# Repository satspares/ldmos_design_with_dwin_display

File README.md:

Work in progress! since 2021

28th April 2026.
New Software and PCB
Improve Graphics.
Add save drive settings per. band.

LDMOS control software and PCB design for dxworld - QRPblog A600 - or similar amps using DWIN display.

PCB design used Kicad.

Software vscode and platformio.

From the DWIN store on aliexpress

DMG80480C050_04W 5inch we need touch version DMG80480C050_04WTC  800x480

DMG80480T050_A5W more cost has case speaker and rs232

DMG80480C043_02W 4.3 inch 800x480 I have this one a bit small for big fingers.

The WTC at the end of the part number is capacitive touch or WTR is resistive touch both are ok but the WTC versions are more sensitive.
Obviously make sure you get a touch version!
Caution some of the displays have a solder link to move from rs232 to ttl.

Some of the later work here is from the excellent ideas of S21RC

G4UFI

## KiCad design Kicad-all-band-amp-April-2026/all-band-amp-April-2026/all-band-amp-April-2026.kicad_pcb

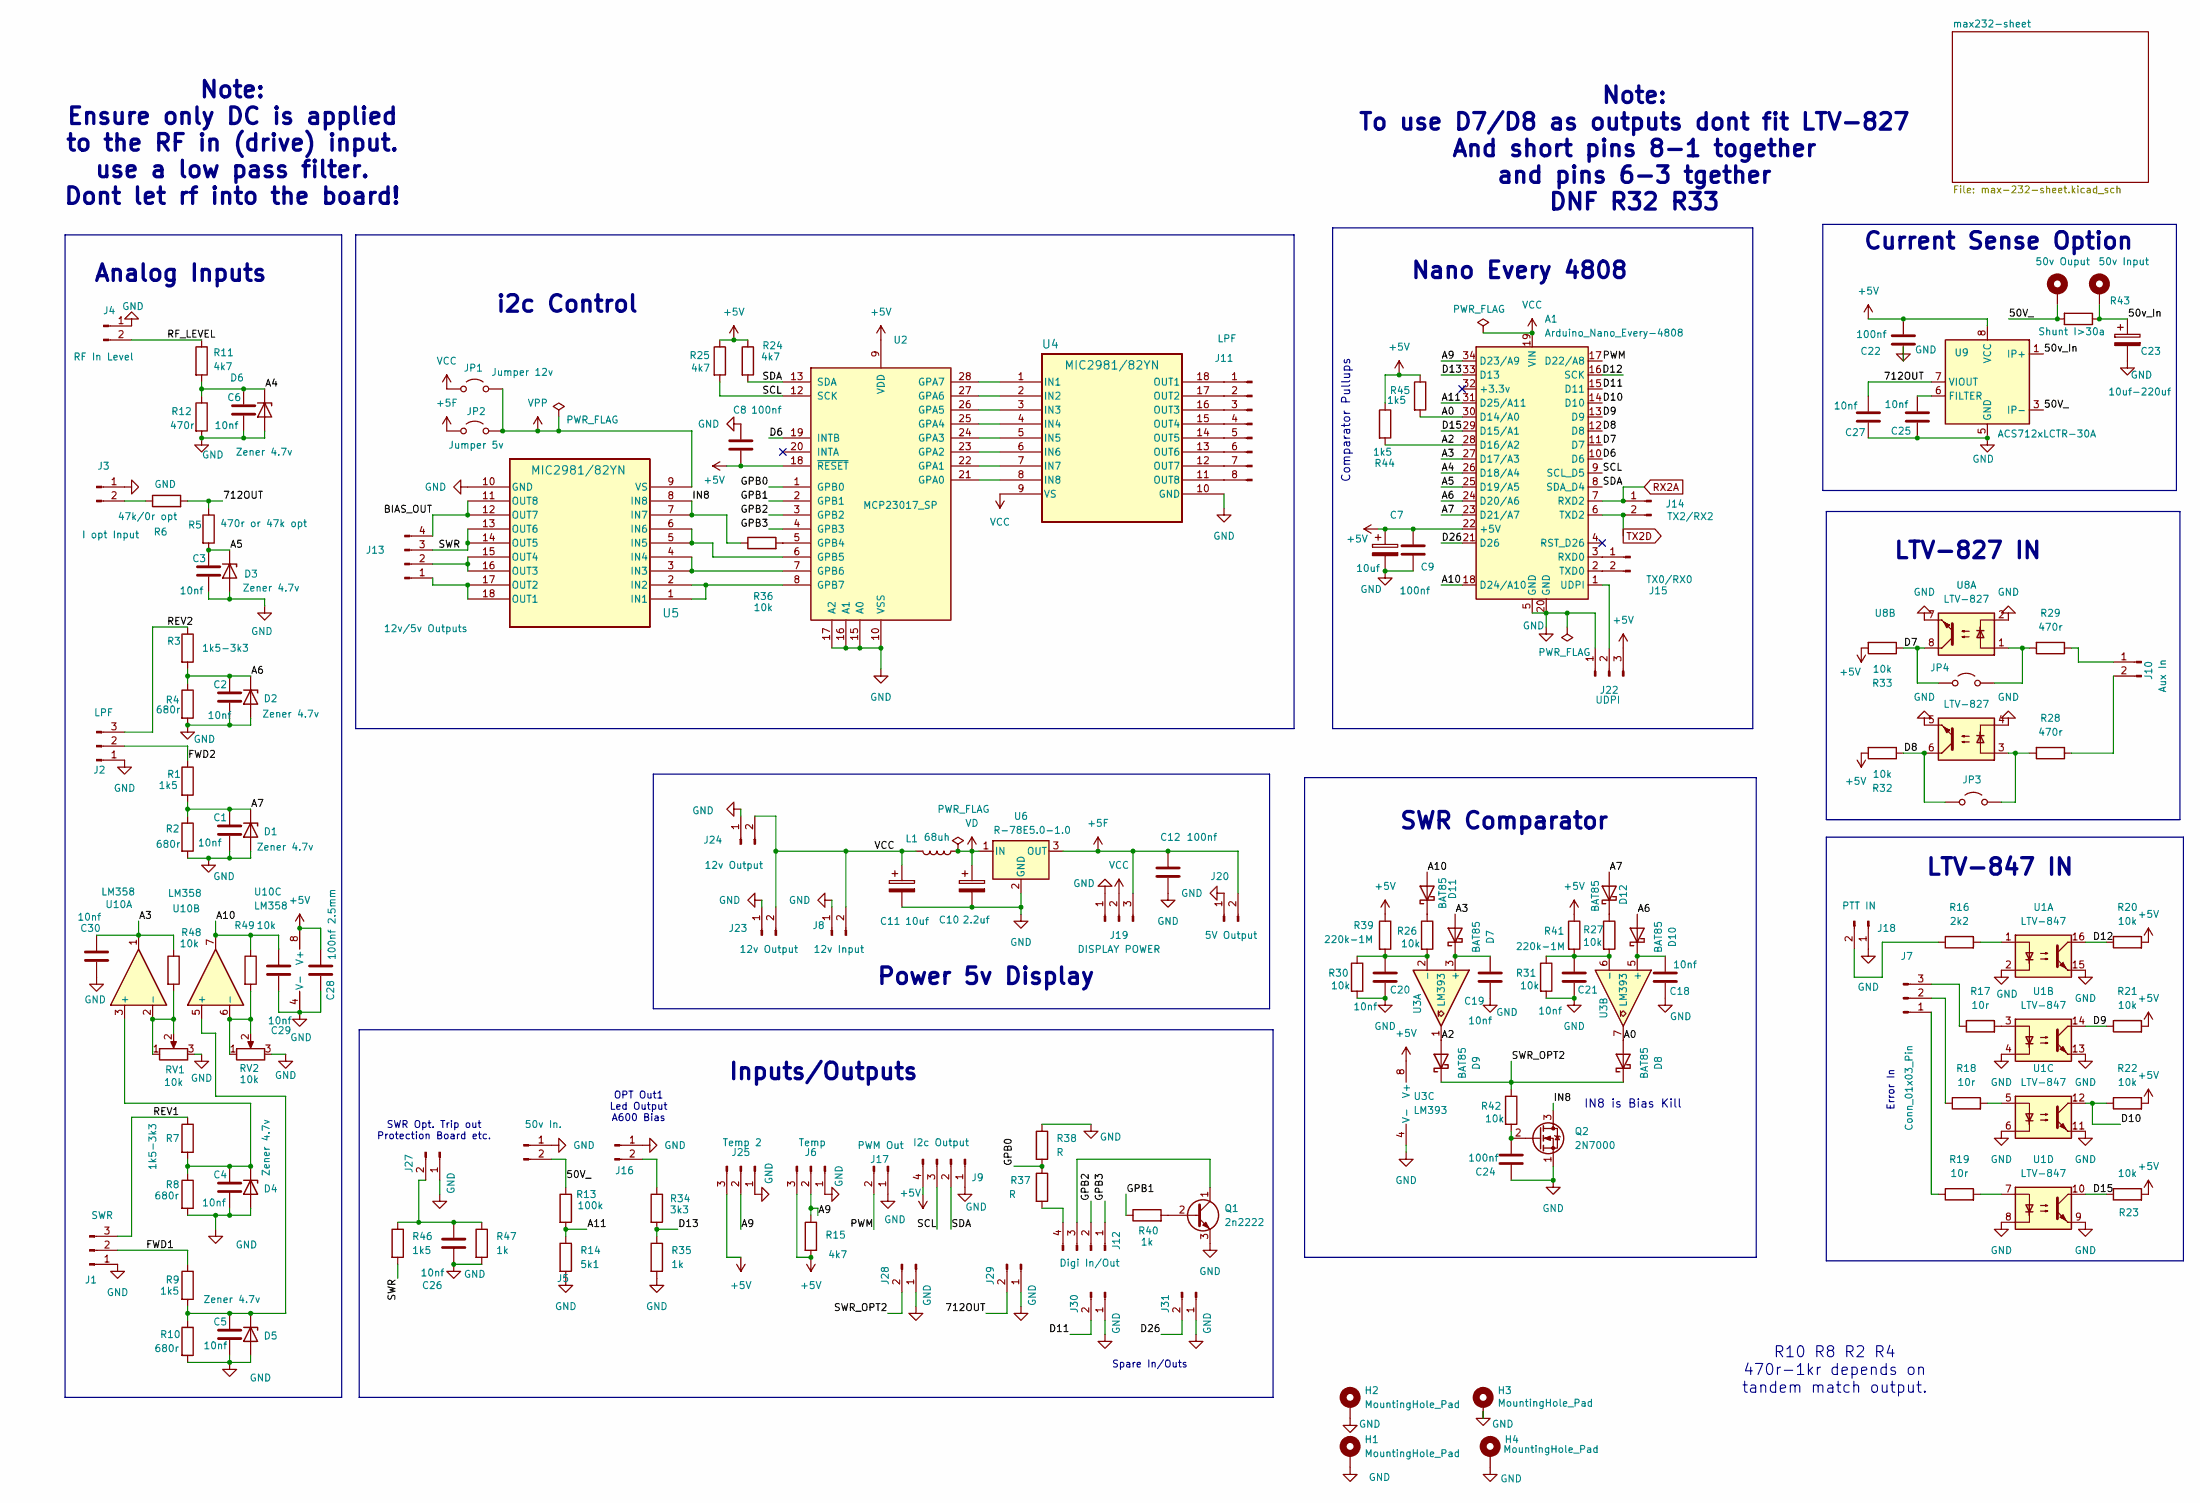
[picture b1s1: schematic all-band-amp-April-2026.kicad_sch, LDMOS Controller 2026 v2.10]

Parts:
A1: Arduino_Nano_Every-4808; DIP-34_W15.24mm
C1, C2, C3, C4, C5, C6, C18, C19, C20, C21, C25, C26, C27, C29, C30: 10nf; C_Disc_D3.4mm_W2.1mm_P2.50mm
C7, C11: 10uf; CP_Radial_D5.0mm_P2.00mm
C8, C9, C12, C22, C24: 100nf; C_Disc_D6.0mm_W2.5mm_P5.00mm
C10: 2.2uf; CP_Radial_D5.0mm_P2.00mm
C23: 10uf-220uf; CP_Radial_D10.0mm_P5.00mm
C28: 100nf 2.5mm; C_Disc_D3.4mm_W2.1mm_P2.50mm
D1, D2, D3, D4, D5, D6: Zener 4.7v; D_DO-35_SOD27_P7.62mm_Horizontal
D7, D8, D9, D10, D11, D12: BAT85; D_DO-35_SOD27_P7.62mm_Horizontal
H1, H2, H3, H4: MountingHole_Pad; MountingHole_3.5mm_Pad_Via
H5: 50v Ouput; PowerPad9mm
H6: 50v Input; PowerPad9mm
J1: SWR; JST_EH_B3B-EH-A_1x03_P2.50mm_Vertical
J2: LPF; JST_EH_B3B-EH-A_1x03_P2.50mm_Vertical
J3: I opt Input; JST_EH_B2B-EH-A_1x02_P2.50mm_Vertical
J4: RF In Level; JST_EH_B2B-EH-A_1x02_P2.50mm_Vertical
J5, J16: 50v In.; JST_EH_B2B-EH-A_1x02_P2.50mm_Vertical
J6: Temp; JST_EH_B3B-EH-A_1x03_P2.50mm_Vertical
J7: Conn_01x03_Pin; JST_EH_B3B-EH-A_1x03_P2.50mm_Vertical
J8: 12v Input; JST_EH_B2B-EH-A_1x02_P2.50mm_Vertical
J9: I2c Output; JST_EH_B4B-EH-A_1x04_P2.50mm_Vertical
J10: Aux In; JST_EH_B2B-EH-A_1x02_P2.50mm_Vertical
J11: LPF; JST_EH_B8B-EH-A_1x08_P2.50mm_Vertical
J12: Digi In/Out; JST_EH_B4B-EH-A_1x04_P2.50mm_Vertical
J13: 12v/5v Outputs; JST_EH_B4B-EH-A_1x04_P2.50mm_Vertical
J14: TX2/RX2; JST_EH_B2B-EH-A_1x02_P2.50mm_Vertical
J15: TX0/RX0; JST_EH_B2B-EH-A_1x02_P2.50mm_Vertical
J17: PWM Out; JST_EH_B2B-EH-A_1x02_P2.50mm_Vertical
J18: PTT IN; JST_EH_B2B-EH-A_1x02_P2.50mm_Vertical
J19: DISPLAY POWER; JST_EH_B3B-EH-A_1x03_P2.50mm_Vertical
J20: 5V Output; JST_EH_B2B-EH-A_1x02_P2.50mm_Vertical
J22: UDPI; JST_EH_B3B-EH-A_1x03_P2.50mm_Vertical
J23, J24: 12v Output; JST_EH_B2B-EH-A_1x02_P2.50mm_Vertical
J25: Temp 2; JST_EH_B3B-EH-A_1x03_P2.50mm_Vertical
J27, J28, J29, J30, J31: SWR trip out; JST_EH_B2B-EH-A_1x02_P2.50mm_Vertical
JP1: Jumper 12v; SolderWire-0.5sqmm_1x02_P4.8mm_D0.9mm_OD2.3mm
JP2: Jumper 5v; SolderWire-0.5sqmm_1x02_P4.8mm_D0.9mm_OD2.3mm
JP3, JP4: Jumper_2_Open; SolderJumper-2_P1.3mm_Open_TrianglePad1.0x1.5mm-mod
L1: 68uh; L_Radial_D7.0mm_P3.00mm
Q1: 2n2222; TO-92_HandSolder
Q2: 2N7000; TO-92_Inline
R1, R9, R44, R45, R46: 1k5; R_Axial_DIN0207_L6.3mm_D2.5mm_P7.62mm_Horizontal
R2, R4, R8, R10: 680r; R_Axial_DIN0207_L6.3mm_D2.5mm_P7.62mm_Horizontal
R3, R7: 1k5-3k3; R_Axial_DIN0207_L6.3mm_D2.5mm_P7.62mm_Horizontal
R5: 470r or 47k opt; R_Axial_DIN0207_L6.3mm_D2.5mm_P7.62mm_Horizontal
R6: 47k/0r opt; R_Axial_DIN0207_L6.3mm_D2.5mm_P7.62mm_Horizontal
R11, R15, R24, R25: 4k7; R_Axial_DIN0207_L6.3mm_D2.5mm_P7.62mm_Horizontal
R12, R28, R29: 470r; R_Axial_DIN0207_L6.3mm_D2.5mm_P7.62mm_Horizontal
R13: 100k; R_Axial_DIN0207_L6.3mm_D2.5mm_P7.62mm_Horizontal
R14: 5k1; R_Axial_DIN0207_L6.3mm_D2.5mm_P7.62mm_Horizontal
R16: 2k2; R_Axial_DIN0207_L6.3mm_D2.5mm_P7.62mm_Horizontal
R17, R18, R19: 10r; R_Axial_DIN0207_L6.3mm_D2.5mm_P7.62mm_Horizontal
R20, R21, R22, R23, R26, R27, R30, R31, R32, R33, R36, R42, R48, R49: 10k; R_Axial_DIN0207_L6.3mm_D2.5mm_P7.62mm_Horizontal
R34: 3k3; R_Axial_DIN0207_L6.3mm_D2.5mm_P7.62mm_Horizontal
R35, R40, R47: 1k; R_Axial_DIN0207_L6.3mm_D2.5mm_P7.62mm_Horizontal
R37, R38: R; R_Axial_DIN0207_L6.3mm_D2.5mm_P7.62mm_Horizontal
R39, R41: 220k-1M; R_Axial_DIN0207_L6.3mm_D2.5mm_P7.62mm_Horizontal
R43: Shunt I>30a; CHSA3920R0003F-MOD
RV1, RV2: 10k; Potentiometer_Bourns_3296W_Vertical
U1: LTV-847; DIP-16_W7.62mm
U2: MCP23017_SP; DIP-28_W7.62mm
U3: LM393; DIP-8_W7.62mm
U4, U5: MIC2981/82YN; DIP-18_W7.62mm_Socket
U6: R-78E5.0-1.0; Converter_DCDC_RECOM_R-78E-0.5_THT
U8: LTV-827; DIP-8_W7.62mm
U9: ACS712xLCTR-30A; SOIC-8_3.9x4.9mm_P1.27mm
U10: LM358; DIP-8_W7.62mm

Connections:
+5F: C12.1, J19.3, J20.2, JP2.1 (A), U6.3 (OUT); also elsewhere on the board
+5V: A1.22 (+5V), C7.1, C8.2, C9.1, C22.1, C28.1, J6.3, J9.4, J22.3, J25.3, R15.2, R20.2, R21.2, R22.2, R23.2, R24.1, R25.1, R32.2, R33.2, R39.1, R41.1, R44.1, R45.1, U2.9 (VDD), U2.18 (~RESET), U3.8 (V+), U9.8 (VCC), U10.8 (V+)
/50V_: H5.1 (1_1), J5.2, R13.1, R43.2, U9.3 (IP-), U9.4 (IP-)
/50v_In: C23.1, H6.1 (1_1), R43.1, U9.1 (IP+), U9.2 (IP+)
/712OUT: C27.1, J29.2, R5.1, R6.2, U9.7 (VIOUT)
/A0: A1.30 (D14/A0), D8.2 (A), R45.2, U3.7
/A2: A1.28 (D16/A2), D9.2 (A), R44.2, U3.1
/A3: A1.27 (D17/A3), C30.1, D7.2 (A), R48.1, U10.1
/A4: A1.26 (D18/A4), C6.1, D6.1 (K), R11.2, R12.1
/A5: A1.25 (D19/A5), C3.1, D3.1 (K), R5.2
/A6: A1.24 (D20/A6), C2.1, D2.1 (K), D10.2 (A), R3.2, R4.1
/A7: A1.23 (D21/A7), C1.1, D1.1 (K), D12.2 (A), R1.2, R2.1
/A9: A1.34 (D23/A9), J6.2, J25.2, R15.1
/A10: A1.18 (D24/A10), C29.1, D11.2 (A), R49.1, U10.7
/A11: A1.31 (D25/A11), R13.2, R14.1
/BIAS_OUT: J13.4, U5.11 (OUT8), U5.12 (OUT7)
/D6: A1.10 (D6), U2.19 (INTB)
/D7: A1.11 (D7), JP4.1 (A), R33.1, U8.8
/D8: A1.12 (D8), JP3.1 (A), R32.1, U8.6
/D9: A1.13 (D9), R21.1, U1.14
/D10: A1.14 (D10), R22.1, U1.12
/D11: A1.15 (D11), J30.2
/D12: A1.16 (SCK), R20.1, U1.16
/D13: A1.33 (D13), R34.2, R35.1
/D15: A1.29 (D15/A1), R23.1, U1.10
/D26: A1.21 (D26), J31.2
/FWD1: J1.2, R9.1
/FWD2: J2.2, R1.1
/GPB0: R37.1, R38.2, U2.1 (GPB0)
/GPB1: R40.1, U2.2 (GPB1)
/GPB2: J12.2, U2.3 (GPB2)
/GPB3: J12.1, U2.4 (GPB3)
/IN8: Q2.3 (D), R36.1, U5.7 (IN7), U5.8 (IN8)
/PWM: A1.17 (D22/A8), J17.2
/REV1: J1.3, R7.1
/REV2: J2.3, R3.1
/RF_LEVEL: J4.2, R11.1
/SCL: A1.9 (SCL_D5), J9.3, R25.2, U2.12 (SCK)
/SDA: A1.8 (SDA_D4), J9.2, R24.2, U2.13 (SDA)
/SWR: J13.3, R46.2, U5.13 (OUT6), U5.14 (OUT5)
/SWR_OPT2: D8.1 (K), D9.1 (K), J28.2, R42.1
GND: A1.5 (GND), A1.20 (GND), C1.2, C2.2, C3.2, C4.2, C5.2, C6.2, C7.2, C8.1, C9.2, C10.2, C11.2, C12.2, C18.1, C19.2, C20.2, C21.2, C22.2, C23.2, C24.2, C25.1, C26.2, C27.2, C28.2, C29.2, C30.2, D1.2 (A), D2.2 (A), D3.2 (A), D4.2 (A), D5.2 (A), D6.2 (A), H1.1 (1_1), H2.1 (1_1), H3.1 (1_1), H4.1 (1_1), J1.1, J2.1, J3.1, J4.1, J5.1, J6.1, J8.1, J9.1, J16.1, J17.1, J18.1, J19.1, J20.1, J22.1, J23.1, J24.1, J25.1, J27.1, J28.1, J29.1, J30.1, J31.1, Q1.3 (E), Q2.1 (S), R2.2, R4.2, R8.2, R10.2, R12.2, R14.2, R30.2, R31.2, R35.2, R38.1, R47.2, RV1.3, RV2.3, U1.2, U1.4, U1.6, U1.8, U1.9, U1.11, U1.13, U1.15, U2.10 (VSS), U2.15 (A0), U2.16 (A1), U2.17 (A2), U3.4 (V-), U4.10 (GND), U5.10 (GND), U6.2 (GND), U8.2, U8.4, U8.5, U8.7, U9.5 (GND), U10.4 (V-); also elsewhere on the board
unnamed: A1.3 (RXD0), J15.1
unnamed: A1.2 (TXD0), J15.2
unnamed: A1.1 (UDPI), J22.2
unnamed: C4.1, D4.1 (K), R7.2, R8.1, U10.3 (+)
unnamed: C5.1, D5.1 (K), R9.2, R10.1, U10.5 (+)
unnamed: C19.1, D7.1 (K), U3.3 (+)
unnamed: C18.2, D10.1 (K), U3.5 (+)
unnamed: D11.1 (K), R26.1
unnamed: D12.1 (K), R27.1
unnamed: J3.2, R6.1
unnamed: J7.1, R19.1
unnamed: J7.2, R18.1
unnamed: J7.3, R17.1
unnamed: J10.1, R29.1
unnamed: J10.2, R28.1
unnamed: J11.1, U4.18 (OUT1)
unnamed: J11.2, U4.17 (OUT2)
unnamed: J11.3, U4.16 (OUT3)
unnamed: J11.4, U4.15 (OUT4)
unnamed: J11.5, U4.14 (OUT5)
unnamed: J11.6, U4.13 (OUT6)
unnamed: J11.7, U4.12 (OUT7)
unnamed: J11.8, U4.11 (OUT8)
unnamed: J12.3, Q1.1 (C)
unnamed: J12.4, R37.2
unnamed: J13.1, U5.17 (OUT2), U5.18 (OUT1)
unnamed: J13.2, U5.15 (OUT4), U5.16 (OUT3)
unnamed: J16.2, R34.1
unnamed: J18.2, R16.1
unnamed: C26.1, J27.2, R46.1, R47.1
unnamed: JP3.2 (B), R28.2, U8.3
unnamed: JP4.2 (B), R29.2, U8.1
unnamed: Q1.2 (B), R40.2
unnamed: C24.1, Q2.2 (G), R42.2
unnamed: R16.2, U1.1
unnamed: R17.2, U1.3
unnamed: R18.2, U1.5
unnamed: R19.2, U1.7
unnamed: U2.21 (GPA0), U4.8 (IN8)
unnamed: U2.22 (GPA1), U4.7 (IN7)
unnamed: U2.23 (GPA2), U4.6 (IN6)
unnamed: U2.24 (GPA3), U4.5 (IN5)
unnamed: U2.25 (GPA4), U4.4 (IN4)
unnamed: U2.26 (GPA5), U4.3 (IN3)
unnamed: U2.27 (GPA6), U4.2 (IN2)
unnamed: U2.28 (GPA7), U4.1 (IN1)
unnamed: R36.2, U2.5 (GPB4)
unnamed: U2.6 (GPB5), U5.5 (IN5), U5.6 (IN6)
unnamed: U2.7 (GPB6), U5.3 (IN3), U5.4 (IN4)
unnamed: U2.8 (GPB7), U5.1 (IN1), U5.2 (IN2)
unnamed: C20.1, R26.2, R30.1, R39.2, U3.2 (-)
unnamed: C21.1, R27.2, R31.1, R41.2, U3.6 (-)
unnamed: C25.2, U9.6 (FILTER)
unnamed: R48.2, RV1.1, RV1.2, U10.2 (-)
unnamed: R49.2, RV2.1, RV2.2, U10.6 (-)
RX2A: A1.7 (RXD2), J14.1; also elsewhere on the board
TX2D: A1.6 (TXD2), J14.2; also elsewhere on the board
VCC: A1.19 (VIN), C11.1, J8.2, J19.2, J23.2, J24.2, JP1.1 (A), L1.2, U4.9 (VS)
VD: C10.1, L1.1, U6.1 (IN)
VPP: JP1.2 (B), JP2.2 (B), U5.9 (VS)

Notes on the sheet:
SWR Opt. Trip out Protection Board etc.
LTV-847 IN
Note: Ensure only DC is applied to the RF in (drive) input. use a low pass filter. Dont let rf into the board!
Analog Inputs
Inputs/Outputs
Current Sense Option
OPT Out1 Led Output A600 Bias
Spare In/Outs
Note: To use D7/D8 as outputs dont fit LTV-827 And short pins 8-1 together and pins 6-3 tgether DNF R32 R33
Nano Every 4808
SWR Comparator
R10 R8 R2 R4 470r-1kr depends on tandem match output.
i2c Control
LTV-827 IN
Error In
IN8 is Bias Kill
Power 5v Display
Comparator Pullups

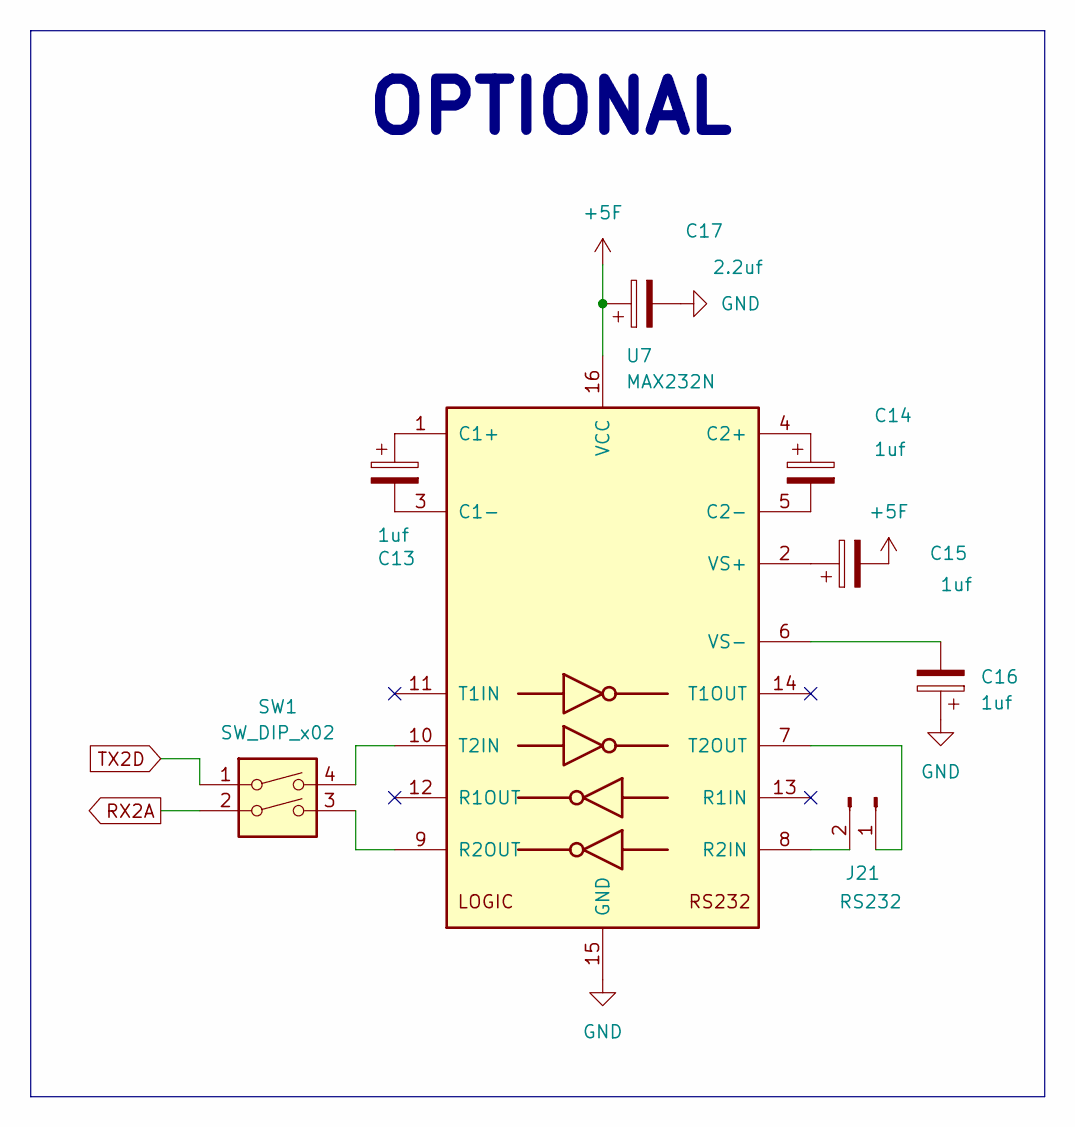
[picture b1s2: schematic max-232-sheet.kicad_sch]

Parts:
C13, C14, C15, C16: 1uf; CP_Radial_D5.0mm_P2.00mm
C17: 2.2uf; CP_Radial_D5.0mm_P2.00mm
J21: RS232; JST_EH_B2B-EH-A_1x02_P2.50mm_Vertical
SW1: SW_DIP_x02; SW_DIP_SPSTx02_Slide_9.78x7.26mm_W7.62mm_P2.54mm
U7: MAX232N; DIP-16_W7.62mm

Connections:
+5F: C15.2, C17.1, U7.16 (VCC); also elsewhere on the board
GND: C16.1, C17.2, U7.15 (GND); also elsewhere on the board
unnamed: J21.1, U7.7 (T2OUT)
unnamed: J21.2, U7.8 (R2IN)
unnamed: C13.1, U7.1 (C1+)
unnamed: C13.2, U7.3 (C1-)
unnamed: C14.1, U7.4 (C2+)
unnamed: C14.2, U7.5 (C2-)
unnamed: SW1.3, U7.9 (R2OUT)
unnamed: SW1.4, U7.10 (T2IN)
unnamed: C15.1, U7.2 (VS+)
unnamed: C16.2, U7.6 (VS-)
RX2A: SW1.2; also elsewhere on the board
TX2D: SW1.1; also elsewhere on the board

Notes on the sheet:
OPTIONAL

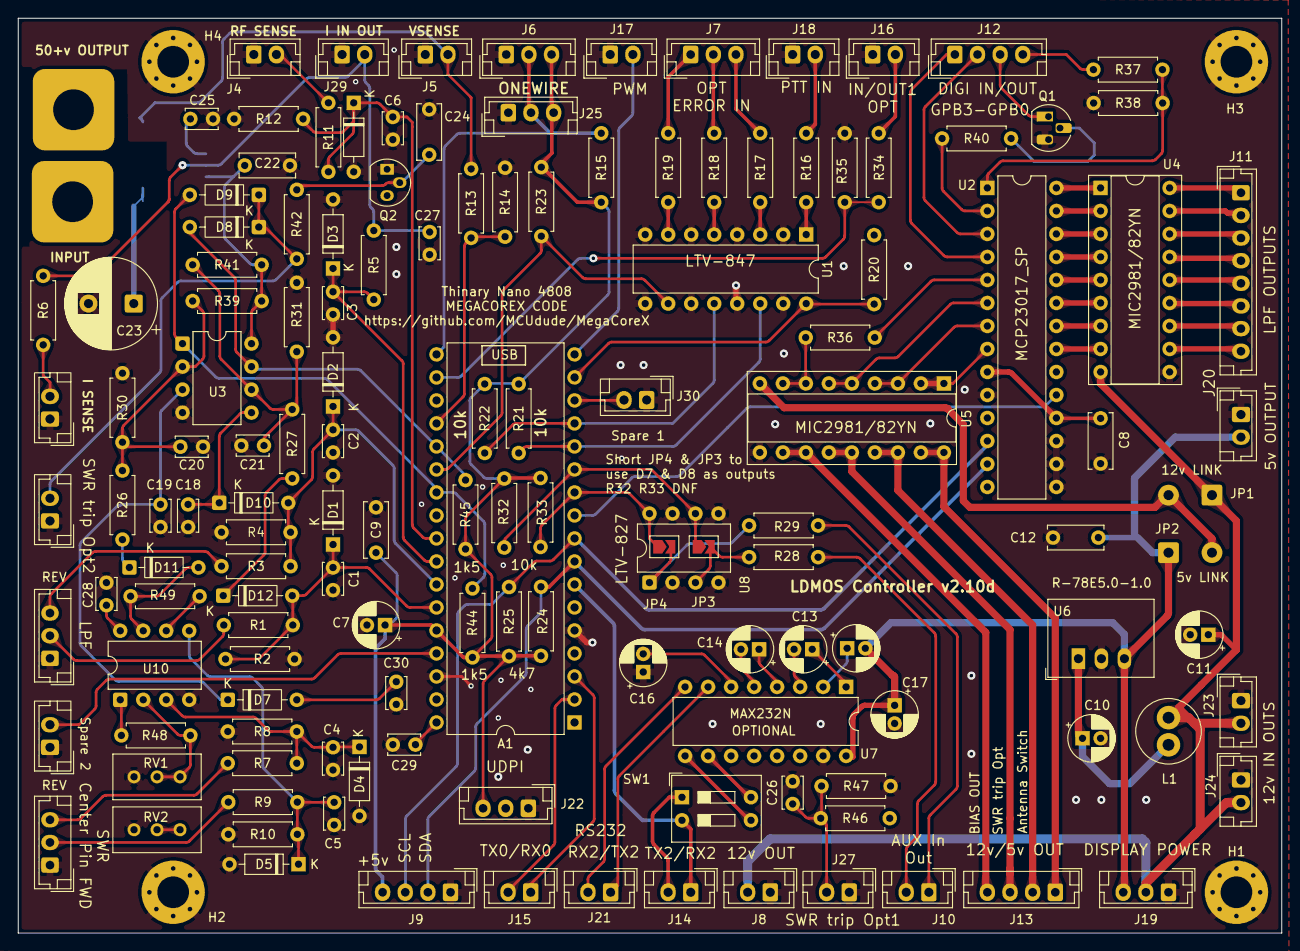
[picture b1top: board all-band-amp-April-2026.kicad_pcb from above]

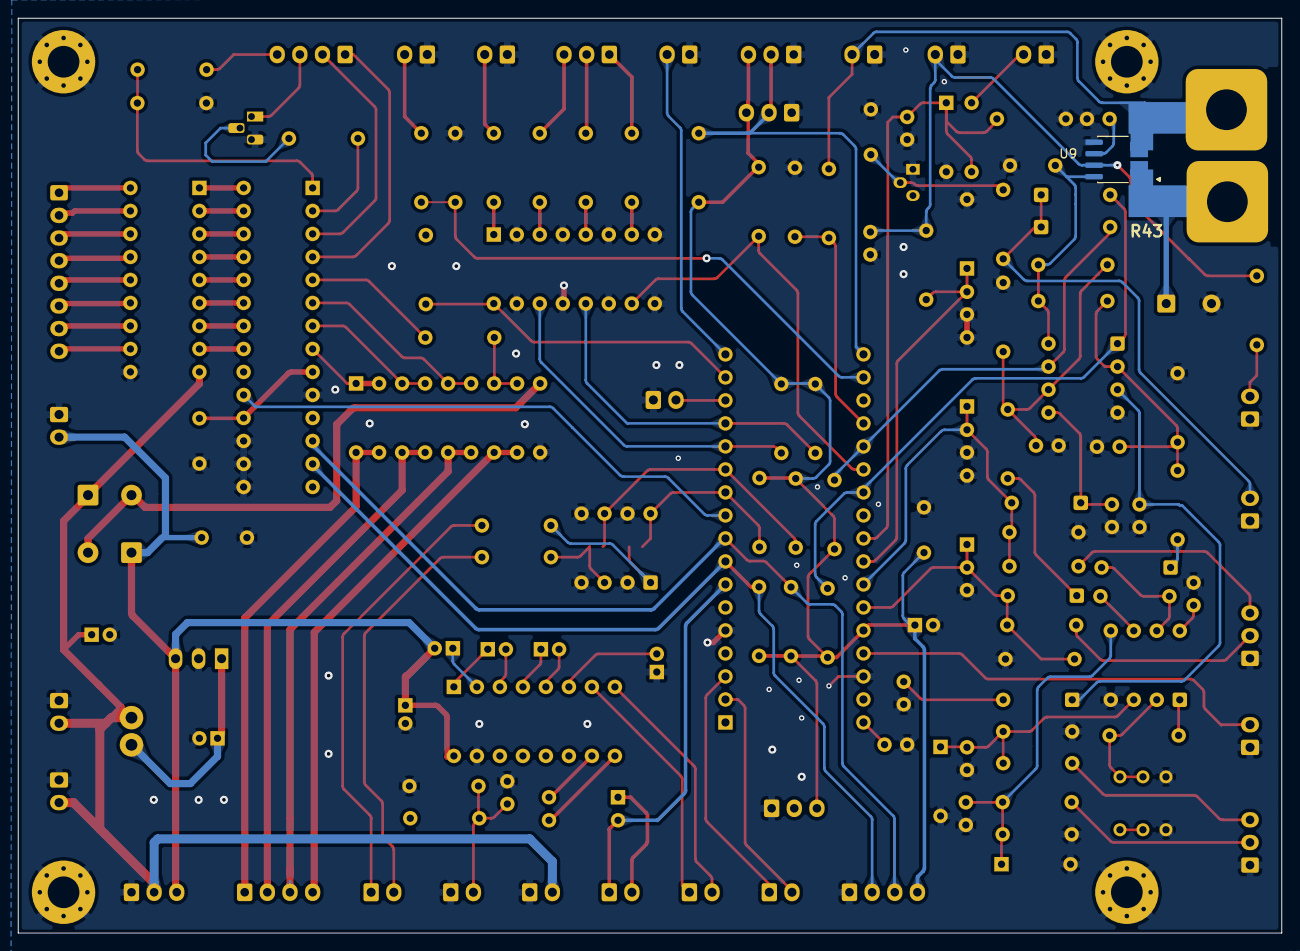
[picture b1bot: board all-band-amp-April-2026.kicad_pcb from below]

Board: 4 copper layers, 139.5 x 101.0 mm, 148 parts (2 on the bottom side), 112 nets.

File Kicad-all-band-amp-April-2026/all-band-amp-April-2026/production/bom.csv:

Designator,Footprint,Quantity,Value,LCSC Part #
A1,DIP-34_W15.24mm,1,Arduino_Nano_Every-4808,
"C1, C18, C19, C2, C20, C21, C25, C26, C27, C29, C3, C30, C4, C5, C6",C_Disc_D3.4mm_W2.1mm_P2.50mm,15,10nf,
"C10, C17",CP_Radial_D5.0mm_P2.00mm,2,2.2uf,
"C11, C7",CP_Radial_D5.0mm_P2.00mm,2,10uf,
"C12, C22, C24, C8, C9",C_Disc_D6.0mm_W2.5mm_P5.00mm,5,100nf,
"C13, C14, C15, C16",CP_Radial_D5.0mm_P2.00mm,4,1uf,
C23,CP_Radial_D10.0mm_P5.00mm,1,10uf-220uf,
C28,C_Disc_D3.4mm_W2.1mm_P2.50mm,1,100nf 2.5mm,
"D1, D2, D3, D4, D5, D6",D_DO-35_SOD27_P7.62mm_Horizontal,6,Zener 4.7v,
"D10, D11, D12, D7, D8, D9",D_DO-35_SOD27_P7.62mm_Horizontal,6,BAT85,
J1,JST_EH_B3B-EH-A_1x03_P2.50mm_Vertical,1,SWR1,
J10,JST_EH_B2B-EH-A_1x02_P2.50mm_Vertical,1,Aux In,
J11,JST_EH_B8B-EH-A_1x08_P2.50mm_Vertical,1,LPF,
J12,JST_EH_B4B-EH-A_1x04_P2.50mm_Vertical,1,Digi In/Out,
J13,JST_EH_B4B-EH-A_1x04_P2.50mm_Vertical,1,12v/5v Outputs,
J14,JST_EH_B2B-EH-A_1x02_P2.50mm_Vertical,1,TX2/RX2,
J15,JST_EH_B2B-EH-A_1x02_P2.50mm_Vertical,1,TX0/RX0,
"J16, J5",JST_EH_B2B-EH-A_1x02_P2.50mm_Vertical,2,50v In.,
J17,JST_EH_B2B-EH-A_1x02_P2.50mm_Vertical,1,PWM Out,
J18,JST_EH_B2B-EH-A_1x02_P2.50mm_Vertical,1,PTT IN,
J19,JST_EH_B3B-EH-A_1x03_P2.50mm_Vertical,1,DISPLAY POWER,
J2,JST_EH_B3B-EH-A_1x03_P2.50mm_Vertical,1,SWR2,
J20,JST_EH_B2B-EH-A_1x02_P2.50mm_Vertical,1,5V Output,
J21,JST_EH_B2B-EH-A_1x02_P2.50mm_Vertical,1,RS232,
J22,JST_EH_B3B-EH-A_1x03_P2.50mm_Vertical,1,UDPI,
"J23, J24",JST_EH_B2B-EH-A_1x02_P2.50mm_Vertical,2,12v Output,
J25,JST_EH_B3B-EH-A_1x03_P2.50mm_Vertical,1,Temp 2,
"J27, J28, J29, J30, J31",JST_EH_B2B-EH-A_1x02_P2.50mm_Vertical,5,SWR trip out,
J3,JST_EH_B2B-EH-A_1x02_P2.50mm_Vertical,1,I opt Input,
J4,JST_EH_B2B-EH-A_1x02_P2.50mm_Vertical,1,RF In Level,
J6,JST_EH_B3B-EH-A_1x03_P2.50mm_Vertical,1,Temp,
J7,JST_EH_B3B-EH-A_1x03_P2.50mm_Vertical,1,Conn_01x03_Pin,
J8,JST_EH_B2B-EH-A_1x02_P2.50mm_Vertical,1,12v Input,
J9,JST_EH_B4B-EH-A_1x04_P2.50mm_Vertical,1,I2c Output,
JP1,SolderWire-0.5sqmm_1x02_P4.8mm_D0.9mm_OD2.3mm,1,Jumper 12v,
JP2,SolderWire-0.5sqmm_1x02_P4.8mm_D0.9mm_OD2.3mm,1,Jumper 5v,
"JP3, JP4",SolderJumper-2_P1.3mm_Open_TrianglePad1.0x1.5mm-mod,2,Jumper_2_Open,
L1,L_Radial_D7.0mm_P3.00mm,1,68uh,
Q1,TO-92_HandSolder,1,2n2222,
Q2,TO-92_Inline,1,2N7000,
"R1, R44, R45, R46, R9",R_Axial_DIN0207_L6.3mm_D2.5mm_P7.62mm_Horizontal,5,1k5,
"R10, R2, R4",R_Axial_DIN0207_L6.3mm_D2.5mm_P7.62mm_Horizontal,3,680r,
"R11, R15, R24, R25",R_Axial_DIN0207_L6.3mm_D2.5mm_P7.62mm_Horizontal,4,4k7,
"R12, R28, R29",R_Axial_DIN0207_L6.3mm_D2.5mm_P7.62mm_Horizontal,3,470r,
R13,R_Axial_DIN0207_L6.3mm_D2.5mm_P7.62mm_Horizontal,1,100k,
R14,R_Axial_DIN0207_L6.3mm_D2.5mm_P7.62mm_Horizontal,1,5k1,
R16,R_Axial_DIN0207_L6.3mm_D2.5mm_P7.62mm_Horizontal,1,2k2,
"R17, R18, R19",R_Axial_DIN0207_L6.3mm_D2.5mm_P7.62mm_Horizontal,3,10r,
"R20, R21, R22, R23, R26, R27, R30, R31, R32, R33, R36, R42, R48, R49",R_Axial_DIN0207_L6.3mm_D2.5mm_P7.62mm_Horizontal,14,10k,
"R3, R7",R_Axial_DIN0207_L6.3mm_D2.5mm_P7.62mm_Horizontal,2,1k5-3k3,
R34,R_Axial_DIN0207_L6.3mm_D2.5mm_P7.62mm_Horizontal,1,3k3,
"R35, R40, R47",R_Axial_DIN0207_L6.3mm_D2.5mm_P7.62mm_Horizontal,3,1k,
"R37, R38",R_Axial_DIN0207_L6.3mm_D2.5mm_P7.62mm_Horizontal,2,R,
"R39, R41",R_Axial_DIN0207_L6.3mm_D2.5mm_P7.62mm_Horizontal,2,220k-1M,
R43,CHSA3920R0003F-MOD,1,Shunt I>30a,
R5,R_Axial_DIN0207_L6.3mm_D2.5mm_P7.62mm_Horizontal,1,470r or 47k opt,
R6,R_Axial_DIN0207_L6.3mm_D2.5mm_P7.62mm_Horizontal,1,47k/0r opt,
R8,R_Axial_DIN0207_L6.3mm_D2.5mm_P7.62mm_Horizontal,1,680rr,
"RV1, RV2",Potentiometer_Bourns_3296W_Vertical,2,10k,
SW1,SW_DIP_SPSTx02_Slide_9.78x7.26mm_W7.62mm_P2.54mm,1,SW_DIP_x02,
U1,DIP-16_W7.62mm,1,LTV-847,
U10,DIP-8_W7.62mm,1,LM358,
U2,DIP-28_W7.62mm,1,MCP23017_SP,
U3,DIP-8_W7.62mm,1,LM393,
"U4, U5",DIP-18_W7.62mm_Socket,2,MIC2981/82YN,
U6,Converter_DCDC_RECOM_R-78E-0.5_THT,1,R-78E5.0-1.0,
U7,DIP-16_W7.62mm,1,MAX232N,
U8,DIP-8_W7.62mm,1,LTV-827,
U9,SOIC-8_3.9x4.9mm_P1.27mm,1,ACS712xLCTR-30A,

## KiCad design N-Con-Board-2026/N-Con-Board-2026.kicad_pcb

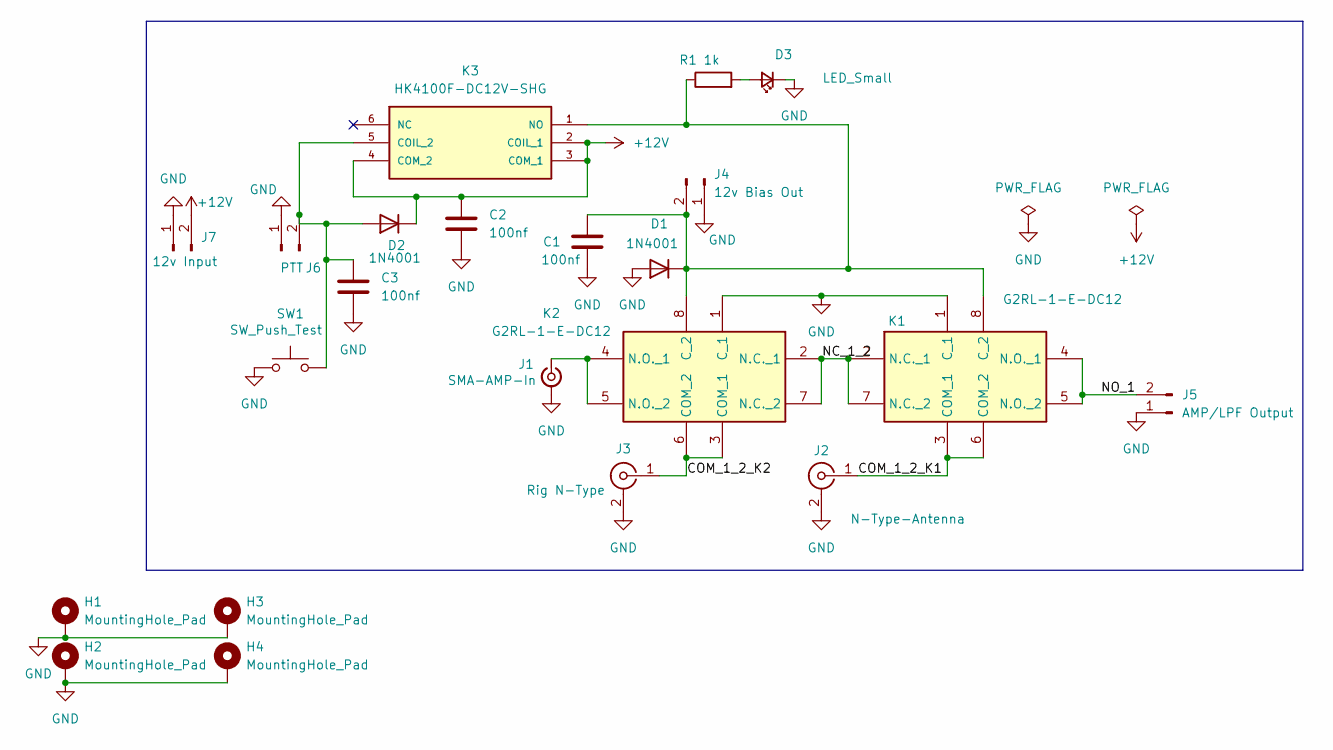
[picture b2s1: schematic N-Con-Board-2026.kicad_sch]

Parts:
C1, C2, C3: 100nf; C_Disc_D6.0mm_W2.5mm_P5.00mm
D1, D2: 1N4001; D_DO-41_SOD81_P10.16mm_Horizontal
D3: LED_Small; LED_D3.0mm
H1, H2, H3, H4: MountingHole_Pad; MountingHole_3.5mm_Pad_Via
J1: SMA-AMP-In; SMA_Amphenol_132134_Vertical
J2: N-Type-Antenna; N_TYPE
J3: Rig N-Type; N_TYPE
J4: 12v Bias Out; JST_EH_B2B-EH-A_1x02_P2.50mm_Vertical
J5: AMP/LPF Output; SolderWirePad_1x02_SMD_11x6mm
J6: PTT; JST_EH_B2B-EH-A_1x02_P2.50mm_Vertical
J7: 12v Input; JST_EH_B2B-EH-A_1x02_P2.50mm_Vertical
K1, K2: G2RL-1-E-DC12; G2RL1EDC24; Mouser Part Number 653-G2RL-1-E-DC12
K3: HK4100F-DC12V-SHG; HK4100FDC5VSHG; MANUFACTURER_PART_NUMBER HK4100F-DC5V-SHG
R1: 1k; R_Axial_DIN0207_L6.3mm_D2.5mm_P7.62mm_Horizontal
SW1: SW_Push_Test; SW_PUSH_6mm

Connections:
+12V: C2.1, D2.1 (K), J7.2, K3.2 (COIL_1), K3.3 (COM_1), K3.4 (COM_2)
/COM_1_2_K1: J2.1 (In), K1.3 (COM_1), K1.6 (COM_2)
/COM_1_2_K2: J3.1 (In), K2.3 (COM_1), K2.6 (COM_2)
/NC_1_2: K1.2 (N.C._1), K1.7 (N.C._2), K2.2 (N.C._1), K2.7 (N.C._2)
/NO_1: J5.2, K1.4 (N.O._1), K1.5 (N.O._2)
GND: C1.2, C2.2, C3.2, D1.2 (A), D3.1 (K), H1.1 (1_1), H2.1 (1_1), H3.1 (1_1), H4.1 (1_1), J1.2 (Ext), J2.2 (Ext), J3.2 (Ext), J4.1, J5.1, J6.1, J7.1, K1.1 (C_1), K2.1 (C_1), SW1.1
unnamed: C1.1, D1.1 (K), J4.2, K1.8 (C_2), K2.8 (C_2), K3.1 (NO), R1.1
unnamed: C3.1, D2.2 (A), J6.2, K3.5 (COIL_2), SW1.2
unnamed: D3.2 (A), R1.2
unnamed: J1.1 (In), K2.4 (N.O._1), K2.5 (N.O._2)

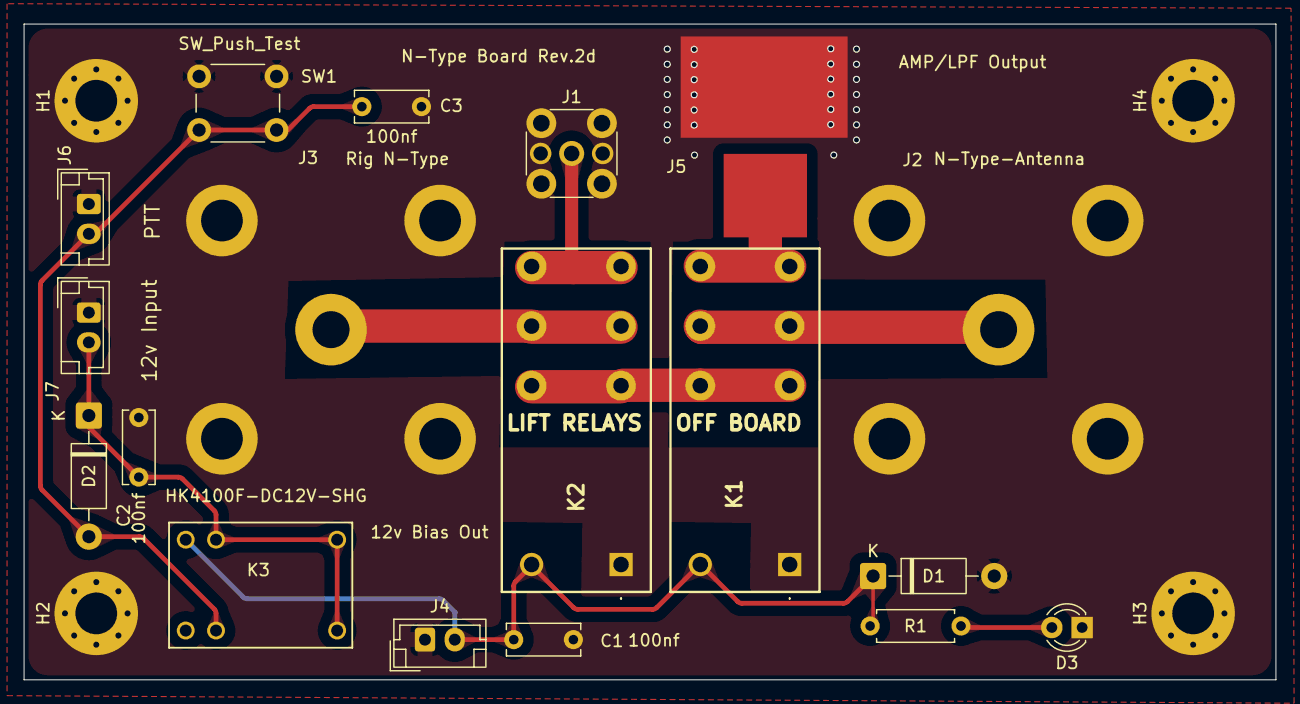
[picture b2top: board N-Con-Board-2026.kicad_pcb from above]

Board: 2 copper layers, 105.0 x 55.0 mm, 22 parts (0 on the bottom side), 10 nets.

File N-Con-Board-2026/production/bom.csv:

Designator,Footprint,Quantity,Value,LCSC Part #
"C1, C2, C3",C_Disc_D6.0mm_W2.5mm_P5.00mm,3,100nf,
"D1, D2",D_DO-41_SOD81_P10.16mm_Horizontal,2,1N4001,
D3,LED_D3.0mm,1,LED_Small,
J1,SMA_Amphenol_132134_Vertical,1,SMA-AMP-In,
J2,N_TYPE,1,N-Type-Antenna,
J3,N_TYPE,1,Rig N-Type,
J4,JST_EH_B2B-EH-A_1x02_P2.50mm_Vertical,1,12v Bias Out,
J5,SolderWirePad_1x02_SMD_11x6mm,1,From AMP/LPF Output,
J6,JST_EH_B2B-EH-A_1x02_P2.50mm_Vertical,1,PTT,
J7,JST_EH_B2B-EH-A_1x02_P2.50mm_Vertical,1,12v Input,
"K1, K2",G2RL1EDC24,2,G2RL-1-E-DC12,
K3,HK4100FDC5VSHG,1,HK4100F-DC12V-SHG,
R1,R_Axial_DIN0207_L6.3mm_D2.5mm_P7.62mm_Horizontal,1,1k,
SW1,SW_PUSH_6mm,1,SW_Push_Test,

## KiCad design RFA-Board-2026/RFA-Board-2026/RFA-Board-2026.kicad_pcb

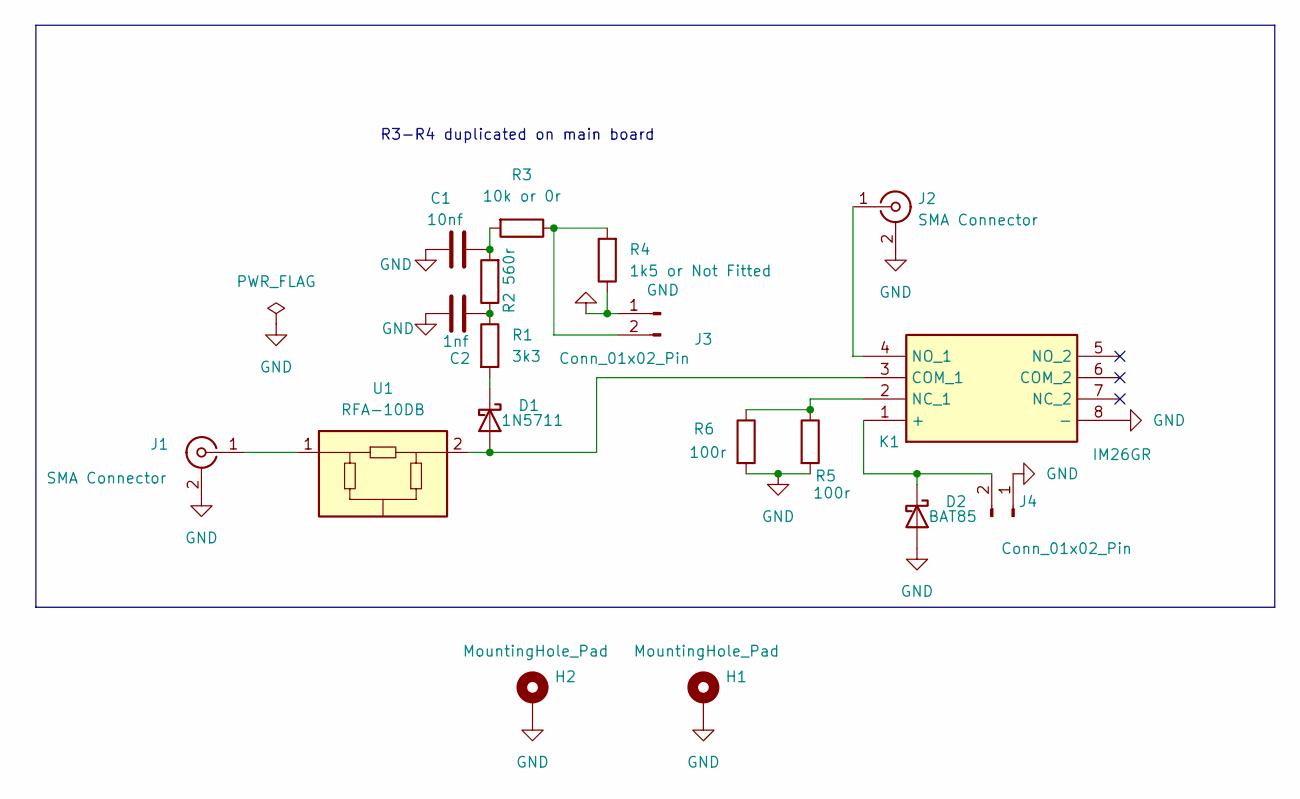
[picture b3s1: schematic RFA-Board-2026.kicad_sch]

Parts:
C1: 10nf; C_1206_3216Metric_Pad1.33x1.80mm_HandSolder
C2: 1nf; C_1206_3216Metric_Pad1.33x1.80mm_HandSolder
D1: 1N5711; D_MELF-RM10_Universal_Handsoldering
D2: BAT85; D_MELF-RM10_Universal_Handsoldering
H1, H2: MountingHole_Pad; MountingHole_3.5mm_Pad_Via
J1, J2: SMA Connector; SMA_Molex_73251-2200_Horizontal_MOD
J3, J4: Conn_01x02_Pin; SolderWirePad_1x02_SMD_11x6mm
K1: IM26GR; IM07GR; Mouser Part Number 655-IM26GR
R1: 3k3; R_1206_3216Metric_Pad1.30x1.75mm_HandSolder
R2: 560r; R_1206_3216Metric_Pad1.30x1.75mm_HandSolder
R3: 10k or 0r; R_1206_3216Metric_Pad1.30x1.75mm_HandSolder
R4: 1k5 or Not Fitted; R_1206_3216Metric_Pad1.30x1.75mm_HandSolder
R5, R6: 100r; RESC11050X120N
U1: RFA-10DB; RFA Attenuator

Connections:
GND: C1.1, C2.1, D2.2 (A), H1.1 (1_1), H2.1 (1_1), J1.2 (Ext), J2.2 (Ext), J3.1, J4.1, K1.8 (-), R4.1, R5.2, R6.2
unnamed: C1.2, R2.2, R3.2
unnamed: C2.2, R1.1, R2.1
unnamed: D1.2 (A), K1.3 (COM_1), U1.2
unnamed: D1.1 (K), R1.2
unnamed: D2.1 (K), J4.2, K1.1 (+)
unnamed: J1.1 (In), U1.1
unnamed: J2.1 (In), K1.4 (NO_1)
unnamed: J3.2, R3.1, R4.2
unnamed: K1.2 (NC_1), R5.1, R6.1

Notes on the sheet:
R3-R4 duplicated on main board

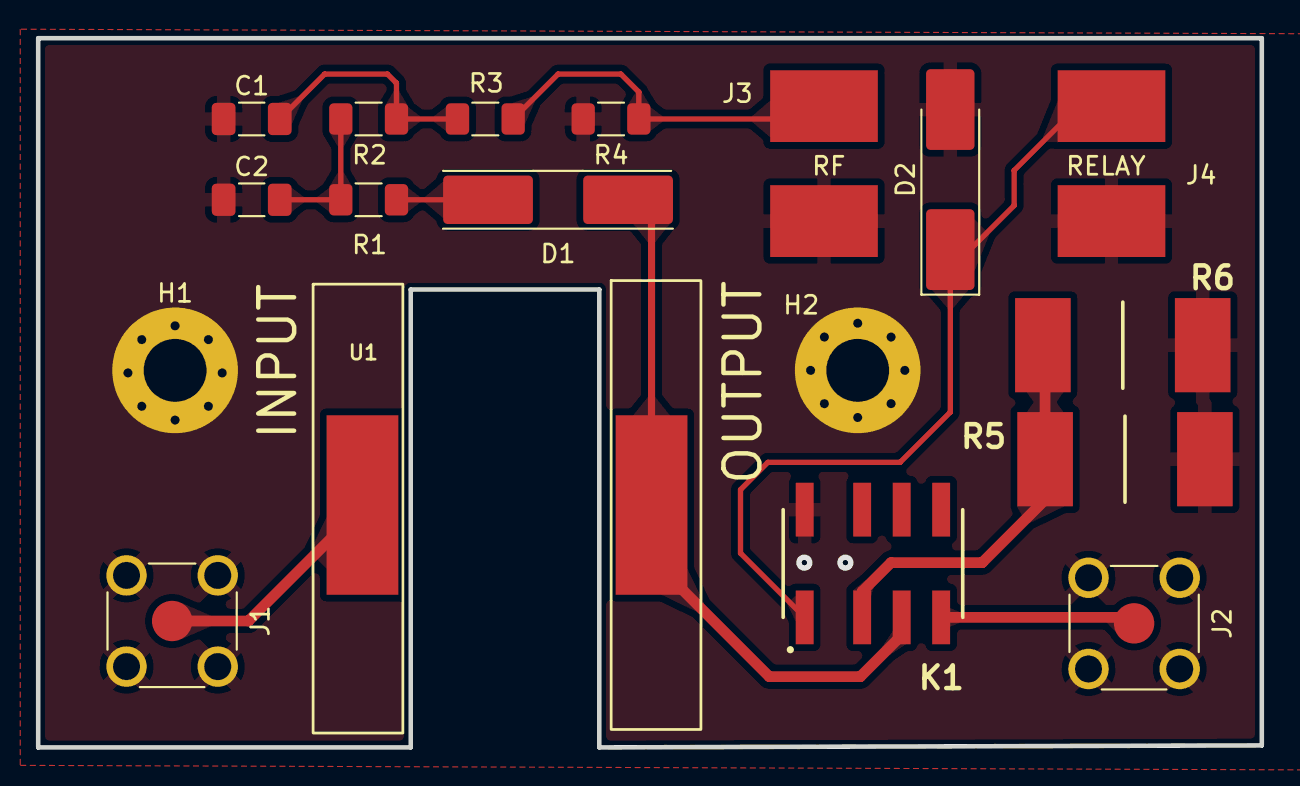
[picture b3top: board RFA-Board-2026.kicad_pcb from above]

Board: 2 copper layers, 68.2 x 39.5 mm, 18 parts (0 on the bottom side), 10 nets.
